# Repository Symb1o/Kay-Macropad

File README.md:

# Kay-Macropad
### Inspiration
I wanted to create a macropad that allowed me to enter in data when I am doing schoolwork. I created a macropad using 10 switches and 1 rp2040.

### Challenges
One thing that was really hard for me was to do was designing the PCB. This was my first time doing it and it took me a long time.

### Specifications
BOM: 
- 10x Cherry MX Switches
- 1x XIAO RP2040
- 10x Blank DSA Keycaps
- 4x M3x16 Bolt
- 4x M3 Heatset

Overall Hackpad

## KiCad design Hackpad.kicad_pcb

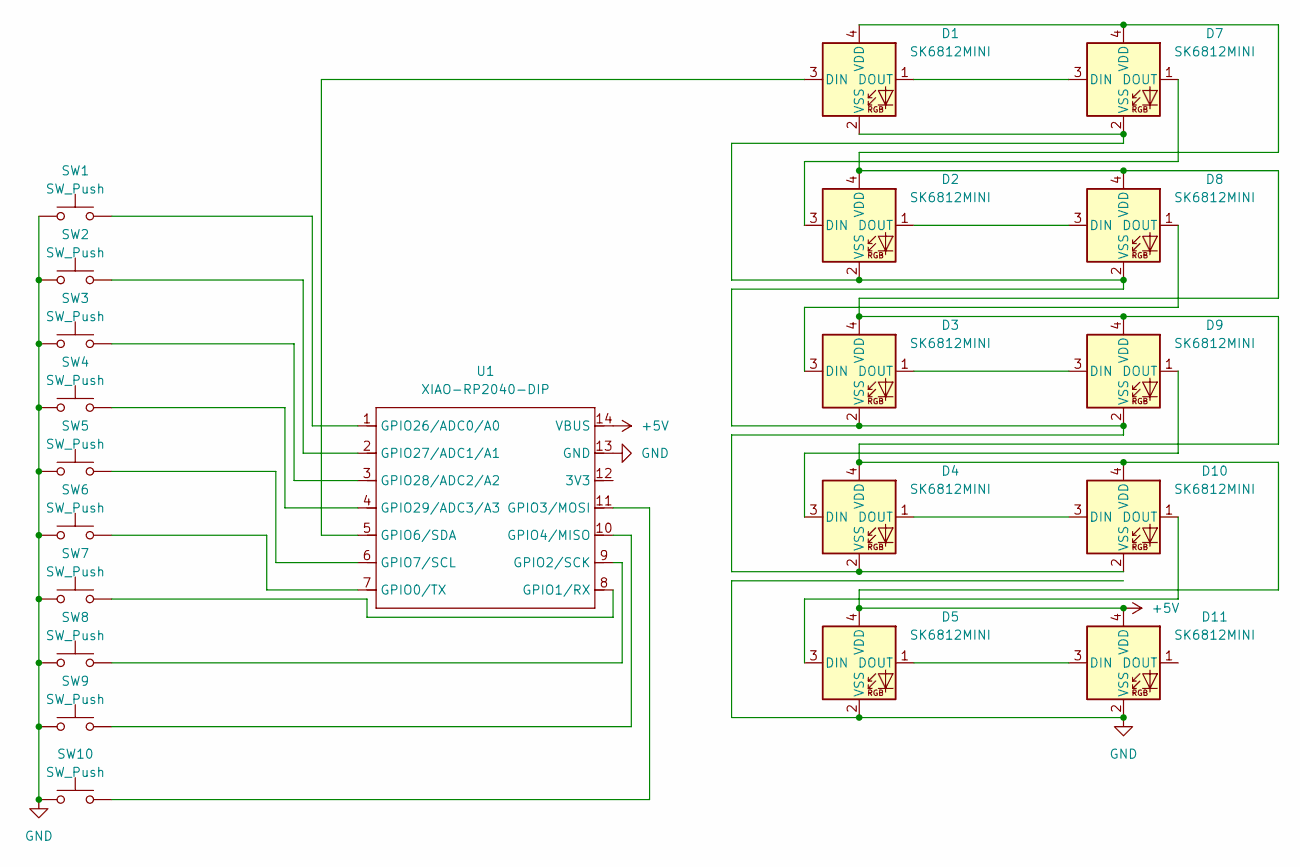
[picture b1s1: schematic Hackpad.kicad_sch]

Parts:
D1, D2, D3, D4, D5, D7, D8, D9, D10, D11: SK6812MINI; LED_SK6812MINI_PLCC4_3.5x3.5mm_P1.75mm
SW1, SW2, SW3, SW4, SW5, SW6, SW7, SW8, SW9, SW10: SW_Push; SW_Cherry_MX_1.00u_PCB
U1: XIAO-RP2040-DIP

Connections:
+5V: D1.4 (VDD), D2.4 (VDD), D3.4 (VDD), D4.4 (VDD), D5.4 (VDD), D7.4 (VDD), D8.4 (VDD), D9.4 (VDD), D10.4 (VDD), D11.4 (VDD), U1.14 (VBUS)
GND: D5.2 (VSS), D11.2 (VSS), SW1.1, SW2.1, SW3.1, SW4.1, SW5.1, SW6.1, SW7.1, SW8.1, SW9.1, SW10.1, U1.13 (GND)
unnamed: D1.3 (DIN), U1.5 (GPIO6/SDA)
unnamed: D1.1 (DOUT), D7.3 (DIN)
unnamed: D1.2 (VSS), D2.2 (VSS), D3.2 (VSS), D4.2 (VSS), D7.2 (VSS), D8.2 (VSS), D9.2 (VSS), D10.2 (VSS)
unnamed: D2.3 (DIN), D7.1 (DOUT)
unnamed: D2.1 (DOUT), D8.3 (DIN)
unnamed: D3.3 (DIN), D8.1 (DOUT)
unnamed: D3.1 (DOUT), D9.3 (DIN)
unnamed: D4.3 (DIN), D9.1 (DOUT)
unnamed: D4.1 (DOUT), D10.3 (DIN)
unnamed: D5.3 (DIN), D10.1 (DOUT)
unnamed: D5.1 (DOUT), D11.3 (DIN)
unnamed: SW6.2, U1.7 (GPIO0/TX)
unnamed: SW7.2, U1.8 (GPIO1/RX)
unnamed: SW8.2, U1.9 (GPIO2/SCK)
unnamed: SW10.2, U1.11 (GPIO3/MOSI)
unnamed: SW9.2, U1.10 (GPIO4/MISO)
unnamed: SW5.2, U1.6 (GPIO7/SCL)
unnamed: SW1.2, U1.1 (GPIO26/ADC0/A0)
unnamed: SW2.2, U1.2 (GPIO27/ADC1/A1)
unnamed: SW3.2, U1.3 (GPIO28/ADC2/A2)
unnamed: SW4.2, U1.4 (GPIO29/ADC3/A3)

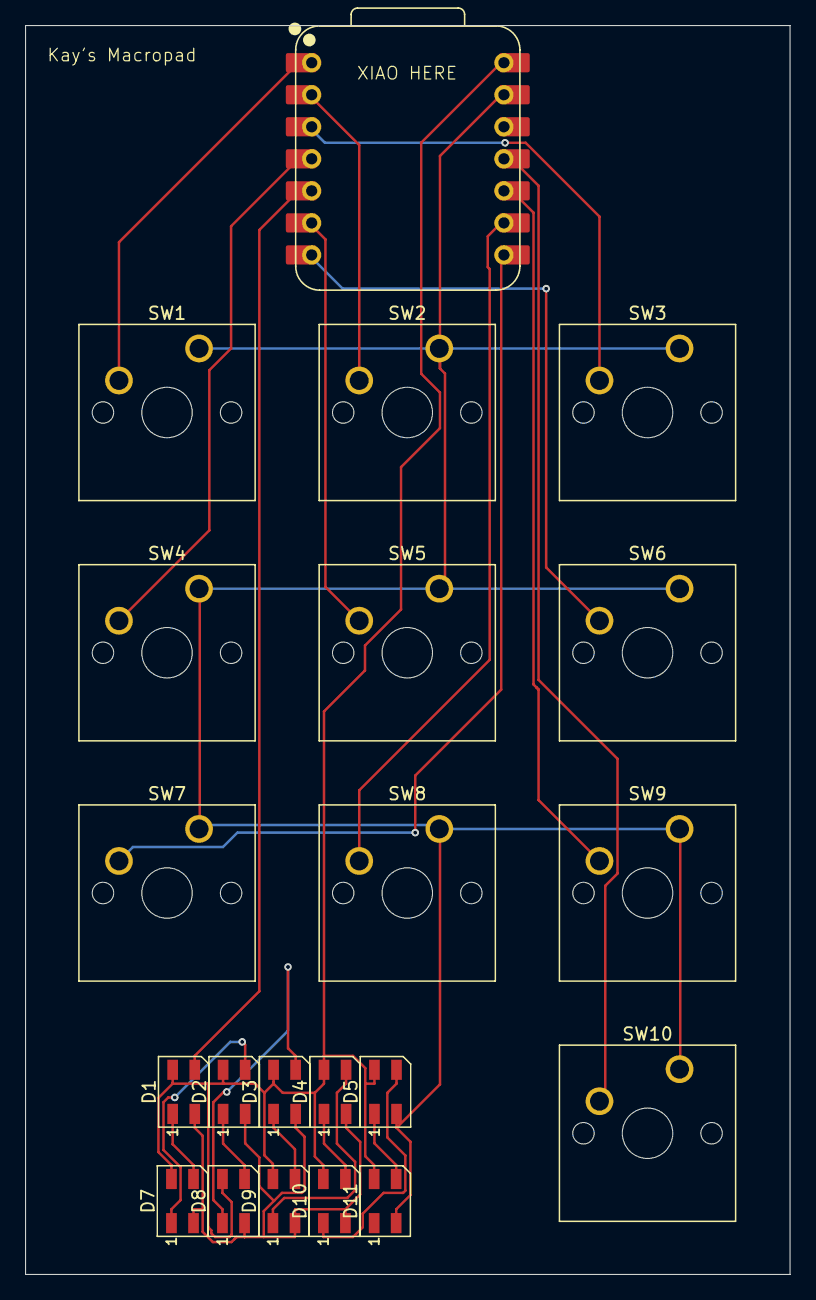
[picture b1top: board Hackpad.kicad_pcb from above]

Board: 2 copper layers, 60.6 x 99.0 mm, 21 parts (0 on the bottom side), 23 nets.
